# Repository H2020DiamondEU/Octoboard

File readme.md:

# Maximum Power Point Tracker for Research-Level Solar Cells

## Overview
This repository documents the design, implementation, and operation of a massively parallel, low-cost Maximum Power Point Tracker (MPPT) for aging and degradation studies of perovskite solar cells. The system integrates custom-designed PCBs and software for efficient tracking and data logging.

## Features
- **Hardware**:

  Octoboards (`Custom-designed PCBs`) for Source Measure Unit (SMU) functions
  - 8 channels per board
  - Modular and scalable design
  - Support for multiple boards via I2C addressing

  Measurement Chuck
   - Allows up to 10 substrates (40 solar cells on a "University of Marburg" cell layout) to be aged in a nitrogen atmosphere.
   - Compact design optimized to fit several chucks under standard solar simulators.  
   - Easy Sample Replacement: Single chucks within the setup can be exchanged during ongoing measurements without breaking the nitrogen atmosphere or interrupting the other measurements within the same sun simulator.  

- **Software**:

  Python-based control system
    - Efficient MPP tracking algorithm
    - Real-time data logging to CSV
    - Multi-board management
    
- **Integration**:

  Full Raspberry Pi compatibility for control and data acquisition

## Repository Structure
```plaintext
├── docs/
│   ├── images/
│   │   ├── EU_logo.png
│   │   ├── EU_logo_funding.png
│   │   ├── diamond_header.png
│   │   ├── octoboard.png
│   │   └── system.png
│   └── D5.2_100_ch_MPP_tracker.pdf
├── hardware/
│   ├── Measurement Chuck Housing CAD Design/
│   │   ├── Assembly.iam 
│   │   ├── Assembly.ipj 
│   │   ├── Bauteil4.ipt 
│   │   ├── Bauteil5.ipt
│   │   ├── Bauteil6.ipt
│   │   ├── chuck_v1.ipt
│   │   ├── DIN_EN_ISO_2338-3_h8x16.ipt 
│   │   ├── DIN_EN_ISO_4762-M2x3.ipt 
│   │   ├── DIN_EN_ISO_4762-M3x5.ipt 
│   │   ├── DIN_EN_ISO_4762-M3x10.ipt 
│   │   ├── DIN_EN_ISO_4762-M3x20.ipt 
│   │   ├── DIN_EN_ISO_7046-2_Z-M2.5x10-8.8-Z1.ipt 
│   │   ├── Glasscheibe.ipt 
│   │   ├── Glassubstrat_25x25x2.2.ipt 
│   │   └── Maske.ipt
│   ├── Measurement Chuck PCB Design/
│   │   ├── SubSheet.kicad_sch
│   │   ├── BOM.csv
│   │   ├── chuck_v1.dsn
│   │   ├── chuck_v1.kicad_pcb
│   │   ├── chuck_v1.kicad_prl
│   │   ├── chuck_v1.kicad_pro
│   │   ├── chuck_v1.kicad_sch
│   │   ├── CPL.csv
│   │   └── gerber.zip
│   ├── Octoboard PCB Design/
│   │   ├── DAC.kicad_sch
│   │   ├── octoboard.kicad_pcb
│   │   ├── octoboard.kicad_prl
│   │   ├── octoboard.kicad_pro
│   │   └── octoboard.kicad_sch
├── software/
│   ├── hardware/
│   │   ├── __init__.py
│   │   ├── channel.py
│   │   ├── constants.py
│   │   ├── i2c.py
│   │   ├── manager.py
│   │   ├── oboard.py
│   │   └── sdac.py
│   ├── tests/
│   │   ├── test_hardware.py
│   │   ├── test_logger.py
│   │   └── test_tracker.py
│   ├── __init__.py
│   ├── cli.py
│   ├── logger.py
│   ├── requirements.txt
│   └── setup.py
└── README.md
```

## Documentation

### 1. Hardware

#### **1.1 Octoboard**
The Octoboard is a custom-designed PCB that forms the core of the MPPT system, providing capabilities for maximum power point tracking in solar cell testing and evaluation.

**Key Components:**
- **MCP23017**: 16-bit I2C I/O expander for digital control
- **MCP4728**: 4-channel DAC for voltage control
- **ADS1115**: 16-bit ADC for precision measurement
- **LMV324**: Quad operational amplifiers for signal conditioning
- **74HC4051**: Analog multiplexers for efficient channel selection

#### Component Specifications

| Component | Type | Key Specifications | Datasheet |
|-----------|------|-------------------|-----------|
| MCP4728 | DAC | 12-bit, 4-channel, I2C | [Datasheet](http://ww1.microchip.com/downloads/en/devicedoc/22187e.pdf) |
| ADS1115 | ADC | 16-bit, 4-channel, I2C | [Datasheet](https://www.ti.com/lit/gpn/ads1115) |
| LMV324 | Op-Amp | Rail-to-rail, low power | [Datasheet](https://www.onsemi.com/download/data-sheet/pdf/lmv321-d.pdf) |
| 74HC4051 | Multiplexer | 8-channel analog | [Datasheet](https://assets.nexperia.com/documents/data-sheet/74HC_HCT4051.pdf) |
| MCP23017 | I/O Expander | 16-bit, I2C | [Datasheet](https://ww1.microchip.com/downloads/aemDocuments/documents/APID/ProductDocuments/DataSheets/MCP23017-Data-Sheet-DS20001952.pdf) |

#### System Architecture
The MPPT system is designed with a hierarchical structure:
1. Central Raspberry Pi controller
2. Multiple Octoboards (8 channels each)
3. I2C communication backbone
4. Integrated sample holder with thermal management

#### **1.2 Measurement Chuck**
The Measurement Chuck allows up to 10 substrates (40 solar cells on a "University of Marburg" cell layout) to be aged under a nitrogen atmosphere.
Due to its compact design, up to eight measurement chucks can be fit in a Solaronix SOLIXON A-45 solar simulator. 

**Operation & Handling**
To replace the substrates inside a chuck:
1. Disconnect the flat ribbon cables and nitrogen supply hoses (quick-connect couplings ensure that the remaining substrates stay in an N₂ atmosphere).
2. Transfer the chuck to a glovebox, where the cells can be exchanged by loosening the screws as shown in the video below.
3. Reinsert the newly equipped chuck into the sun simulator and attach it to the cables and supply hoses. 

<div style="display: flex; justify-content: flex-start;">
    
</div>

### 2. Software

#### Installation

1. Clone the repository:
```bash
git clone https://github.com/H2020DiamondEU/octoboard.git
cd octoboard
```

2. Install dependencies:
```bash
pip install -r software/requirements.txt
```

3. Install the package:
```bash
pip install -e .
```

#### Usage

1. Basic operation:
```python
from software import OBoardManager

# Initialize manager with I2C bus number
manager = OBoardManager(i2c_num=1)

# Start MPP tracking on all channels
manager.cycle_all_channels(iterations_per_channel=10)
```

2. Command-line interface:
```bash
python -m software.cli 1  # Start tracking on I2C bus 1
```

### 3. Data Management

Data is stored in CSV format with the following structure:
- Location: `data/[board_id]_channel_[n]_data.csv`
- Format: timestamp, voltage, current, power, temperature

### 4. Troubleshooting

Common issues and solutions:
1. I2C Communication Errors
   - Check bus number and device addresses
   - Verify cable connections
   - Check for address conflicts

2. Measurement Instability
   - Verify power supply stability
   - Check contact resistance

## License
This project is licensed under the MIT License. See `LICENSE` for details.

## Links
- [Project Website](https://diamond-horizon.eu/)
- [European Commission Project Page](https://cordis.europa.eu/project/id/101084124)
- [Deliverable Documentation](https://ec.europa.eu/research/participants/documents/downloadPublic?documentIds=080166e50d1470c5&appId=PPGMS)

## Contact
For further information on integrating this measurement system into your PV lab, please contact:
- **Lukas Wagner**, Physics of Solar Energy Conversion Group, Philipps-University Marburg, Germany.
- **Clemens Baretzky**, Fraunhofer Institute for Solar Energy Systems ISE, Germany.

<div style="display: flex; justify-content: flex-start;">
    
</div> 

## Acknowledgments
This design was developed at the **University of Marburg** and **Fraunhofer ISE**.
The project is funded by the European Union in the Horizon 2.5. Climate, Energy and Mobility programme under Grant Agreement No. 101084124. Views and opinions expressed are however those of the author(s) only and do not necessarily reflect those of the European Union. Neither the European Union nor the granting authority can be held responsible for them.

<div style="display: flex; justify-content: flex-start;">
    
</div>

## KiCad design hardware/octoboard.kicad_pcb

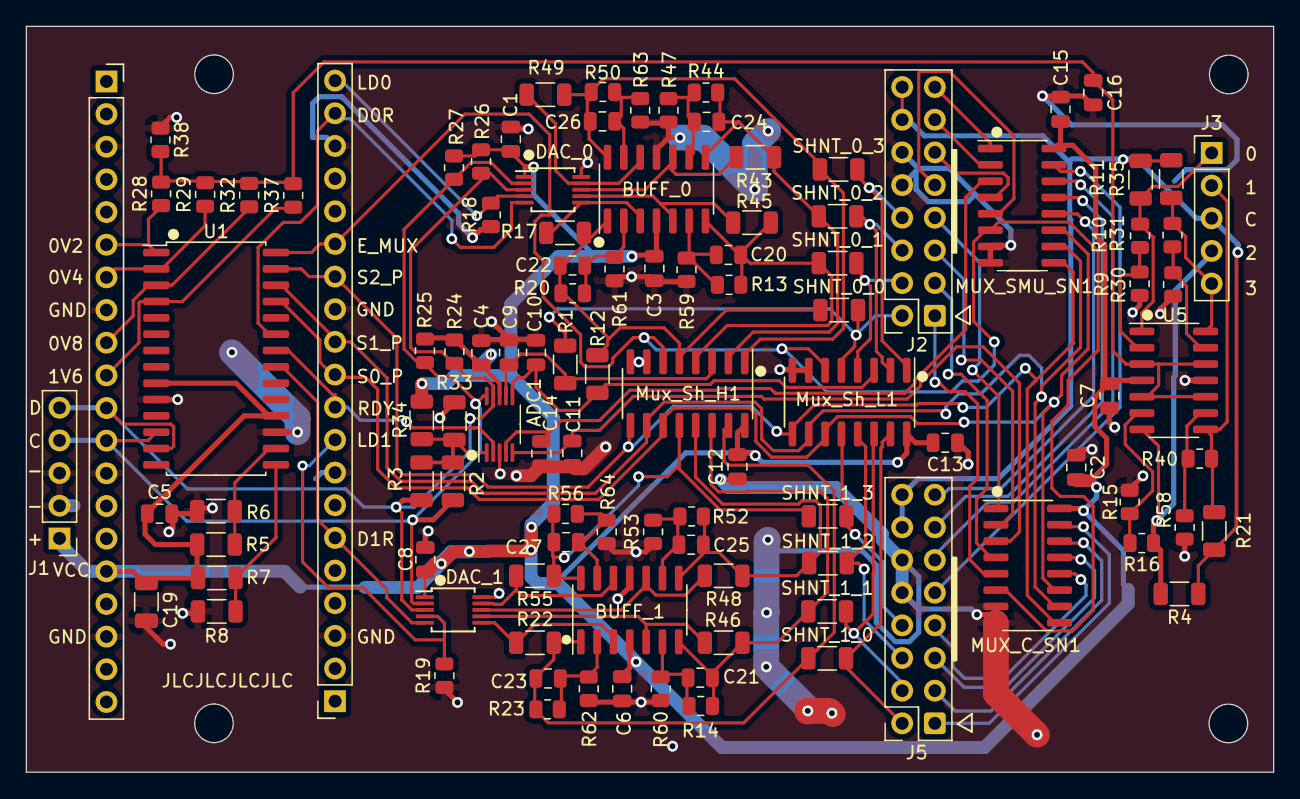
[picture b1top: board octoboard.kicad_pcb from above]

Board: 2 copper layers, 97.0 x 58.0 mm, 107 parts (0 on the bottom side), 82 nets.

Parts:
ADC1: ADS1115IDGS; VSSOP-10_3x3mm_P0.5mm
BUFF_0, BUFF_1: LMV324; SOIC-14_3.9x8.7mm_P1.27mm
C1, C2, C3, C4, C5, C6, C7, C8, C9, C10, C11, C12, C13, C14, C15, C16: 0.1µ; C_0805_2012Metric
C19: 1µ; C_1206_3216Metric
C20, C21, C22, C23, C24, C25, C26, C27: 22p; C_0805_2012Metric
DAC_0, DAC_1: MCP4728; MSOP-10_3x3mm_P0.5mm
J1, J3: Conn_01x05_Pin; PinHeader_1x05_P2.54mm_Vertical
J2, J5: Conn_02x08_Odd_Even; IDC-Header_2x08_P2.54mm_Vertical_NO_SHROUD
MUX_C_SN1: 74HC4051; SOIC-16_3.9x9.9mm_P1.27mm
MUX_SMU_SN1: 74HC4051; SOIC-16_3.9x9.9mm_P1.27mm
Mux_Sh_H1: 74HC4051; SOIC-16_3.9x9.9mm_P1.27mm
Mux_Sh_L1: 74HC4051; SOIC-16_3.9x9.9mm_P1.27mm
R1, R2, R3, R5, R6, R7, R8, R12, R17, R22, R33, R34, R43, R45, R46, R48, R49, R55: 0; R_1206_3216Metric
R4, R11, R21, R35: 10; R_1206_3216Metric
R9, R10, R13, R14, R15, R16, R20, R23, R30, R31, R40, R44, R47, R50, R52, R53, R56, R58, R59, R60, R61, R62, R63, R64: 12k; R_0805_2012Metric
R18, R19, R28: 47k; R_0805_2012Metric
R24, R25, R26, R27, R37: 4.7K; R_0805_2012Metric
R29: 22k; R_0805_2012Metric
R32, R38: 10k; R_0805_2012Metric
RPI_20, RPI_40: Conn_01x20_Female; PinSocket_1x20_P2.54mm_Vertical
SHNT_0_0, SHNT_0_1, SHNT_0_2, SHNT_0_3, SHNT_1_0, SHNT_1_1, SHNT_1_2, SHNT_1_3: 20; R_1206_3216Metric
U1: MCP23017_SO; SOIC-28W_7.5x17.9mm_P1.27mm
U5: LMV324DR2G; SOIC-14_3.9x8.7mm_P1.27mm

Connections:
+3.3V: ADC1.8 (VDD), BUFF_0.4 (V+), BUFF_1.4 (V+), C1.2, C2.2, C3.2, C4.1, C5.1, C6.2, C7.2, C8.2, C12.2, C13.2, C15.2, C19.2, DAC_0.1 (VDD), DAC_1.1 (VDD), J1.1, MUX_C_SN1.16 (VCC), MUX_SMU_SN1.16 (VCC), Mux_Sh_H1.16 (VCC), Mux_Sh_L1.16 (VCC), R5.2, R7.2, R24.2, R25.2, R26.2, R27.2, R34.2, RPI_20.16, U1.9 (VDD), U1.18 (~RESET), U5.4 (V+)
A0_mult: ADC1.4 (AIN0), C14.2, MUX_SMU_SN1.3 (A)
A1_mult: ADC1.5 (AIN1), C11.2, MUX_C_SN1.3 (A)
A2_mult: ADC1.6 (AIN2), C10.2, Mux_Sh_L1.3 (A), R12.1
A3_mult: ADC1.7 (AIN3), C9.2, Mux_Sh_H1.3 (A), R1.1
ADC_1_RDY: ADC1.2 (ALERT/RDY), RPI_40.10, U1.22 (GPA1)
C_SENS_0_0: J2.1, MUX_C_SN1.5 (A5)
C_SENS_0_1: J2.3, MUX_C_SN1.4 (A7)
C_SENS_0_2: J2.5, MUX_C_SN1.2 (A6)
C_SENS_0_3: J2.7, MUX_C_SN1.1 (A4)
C_SENS_1_0: J5.1, MUX_C_SN1.15 (A2)
C_SENS_1_1: J5.3, MUX_C_SN1.14 (A1)
C_SENS_1_2: J5.5, MUX_C_SN1.13 (A0)
C_SENS_1_3: J5.7, MUX_C_SN1.12 (A3)
DAC_0_LDAC: DAC_0.4 (~LDAC), R18.2, RPI_40.20
DAC_0_RDY: DAC_0.5 (RDY/~BSY), RPI_40.19, U1.23 (GPA2)
DAC_1_LDAC: DAC_1.4 (~LDAC), R19.2, RPI_40.9
DAC_1_RDY: DAC_1.5 (RDY/~BSY), RPI_40.6, U1.21 (GPA0)
DAC_BUFF_0_0: BUFF_0.1, C22.2, Mux_Sh_H1.5 (A5), R12.2, R17.2, R20.2, SHNT_0_0.1
DAC_BUFF_0_1: BUFF_0.7, C20.2, Mux_Sh_H1.4 (A7), R13.2, R45.2, SHNT_0_1.1
DAC_BUFF_0_2: BUFF_0.8, C24.2, Mux_Sh_H1.2 (A6), R43.2, R44.2, SHNT_0_2.1
DAC_BUFF_0_3: BUFF_0.14, C26.2, Mux_Sh_H1.1 (A4), R49.2, R50.2, SHNT_0_3.1
DAC_BUFF_1_0: BUFF_1.1, C23.2, Mux_Sh_H1.15 (A2), R22.2, R23.2, SHNT_1_0.1
DAC_BUFF_1_1: BUFF_1.7, C21.2, Mux_Sh_H1.14 (A1), R14.2, R46.2, SHNT_1_1.1
DAC_BUFF_1_2: BUFF_1.8, C25.2, Mux_Sh_H1.13 (A0), R48.2, R52.2, SHNT_1_2.1
DAC_BUFF_1_3: BUFF_1.14, C27.2, Mux_Sh_H1.12 (A3), R55.2, R56.2, SHNT_1_3.1
E_mult_1: MUX_C_SN1.6 (~E), MUX_SMU_SN1.6 (~E), Mux_Sh_H1.6 (~E), Mux_Sh_L1.6 (~E), RPI_40.15, U1.28 (GPA7)
GND: ADC1.3 (GND), BUFF_0.11 (V-), BUFF_1.11 (V-), C1.1, C2.1, C3.1, C4.2, C5.2, C6.1, C7.1, C8.1, C9.1, C10.1, C11.1, C12.1, C13.1, C14.1, C15.1, C16.2, C19.1, DAC_0.10 (VSS), DAC_1.10 (VSS), J1.2, J1.3, J2.10, J2.12, J5.10, J5.12, MUX_C_SN1.7 (VEE), MUX_C_SN1.8 (GND), MUX_SMU_SN1.7 (VEE), MUX_SMU_SN1.8 (GND), Mux_Sh_H1.7 (VEE), Mux_Sh_H1.8 (GND), Mux_Sh_L1.7 (VEE), Mux_Sh_L1.8 (GND), R6.1, R8.1, R9.1, R15.1, R18.1, R19.1, R30.1, R33.2, R38.1, R47.1, R53.1, R58.1, R59.1, R60.1, R61.1, R62.1, R63.1, R64.1, RPI_20.3, RPI_20.8, RPI_20.13, RPI_20.18, RPI_40.3, RPI_40.8, RPI_40.13, RPI_40.18, U1.10 (VSS), U1.17 (A2), U5.11 (V-)
I2C0_SCL: ADC1.10 (SCL), DAC_0.2 (SCL), DAC_1.2 (SCL), J1.4, R2.2, R25.1, R27.1, RPI_20.12, U1.12 (SCK)
I2C0_SDA: ADC1.9 (SDA), DAC_0.3 (SDA), DAC_1.3 (SDA), J1.5, R3.2, R24.1, R26.1, RPI_20.11, U1.13 (SDA)
unnamed: ADC1.1 (ADDR), R2.1, R3.1, R33.1, R34.1
unnamed: BUFF_0.3 (+), DAC_0.6 (VOUTA), R17.1
unnamed: BUFF_0.2 (-), C22.1, R20.1, R61.2
unnamed: BUFF_0.5 (+), DAC_0.7 (VOUTB), R45.1
unnamed: BUFF_0.6 (-), C20.1, R13.1, R59.2
unnamed: BUFF_0.10 (+), DAC_0.8 (VOUTC), R43.1
unnamed: BUFF_0.9 (-), C24.1, R44.1, R47.2
unnamed: BUFF_0.12 (+), DAC_0.9 (VOUTD), R49.1
unnamed: BUFF_0.13 (-), C26.1, R50.1, R63.2
unnamed: BUFF_1.3 (+), DAC_1.6 (VOUTA), R22.1
unnamed: BUFF_1.2 (-), C23.1, R23.1, R62.2
unnamed: BUFF_1.5 (+), DAC_1.7 (VOUTB), R46.1
unnamed: BUFF_1.6 (-), C21.1, R14.1, R60.2
unnamed: BUFF_1.10 (+), DAC_1.8 (VOUTC), R48.1
unnamed: BUFF_1.9 (-), C25.1, R52.1, R53.2
unnamed: BUFF_1.12 (+), DAC_1.9 (VOUTD), R55.1
unnamed: BUFF_1.13 (-), C27.1, R56.1, R64.2
unnamed: R7.1, R8.2, U1.15 (A0)
unnamed: R5.1, R6.2, U1.16 (A1)
unnamed: C16.1, R28.2, R29.2, R32.2, R37.2, R38.2, U5.3 (+), U5.5 (+), U5.10 (+), U5.12 (+)
unnamed: R9.2, R10.1, U5.2 (-)
unnamed: R15.2, R16.1, U5.6 (-)
unnamed: R40.1, R58.2, U5.9 (-)
unnamed: R30.2, R31.1, U5.13 (-)
S0_PLX: MUX_C_SN1.11 (S0), MUX_SMU_SN1.11 (S0), Mux_Sh_H1.11 (S0), Mux_Sh_L1.11 (S0), RPI_40.11, U1.25 (GPA4)
S1_PLX: MUX_C_SN1.10 (S1), MUX_SMU_SN1.10 (S1), Mux_Sh_H1.10 (S1), Mux_Sh_L1.10 (S1), RPI_40.12, U1.26 (GPA5)
S2_PLX: MUX_C_SN1.9 (S2), MUX_SMU_SN1.9 (S2), Mux_Sh_H1.9 (S2), Mux_Sh_L1.9 (S2), RPI_40.14, U1.27 (GPA6)
SDAC_A_0V2: R28.1, RPI_20.6, U1.1 (GPB0)
SDAC_A_0V4: R29.1, RPI_20.7, U1.2 (GPB1)
SDAC_B_0V8: R32.1, RPI_20.9, U1.3 (GPB2)
SDAC_B_1V6: R37.1, RPI_20.10, U1.4 (GPB3)
SDAC_V0: J3.1, R10.2, R11.2, U5.1
SDAC_V1: J3.2, R21.2, R40.2, U5.8
SDAC_V2: J3.4, R4.2, R16.2, U5.7
SDAC_V3: J3.5, R31.2, R35.2, U5.14
SMU_Common: J2.14, J2.16, J3.3, J5.14, J5.16, R4.1, R11.1, R21.1, R35.1
SMU_OUT_0_0: J2.2, Mux_Sh_L1.5 (A5), R1.2, SHNT_0_0.2
SMU_OUT_0_1: J2.4, Mux_Sh_L1.4 (A7), SHNT_0_1.2
SMU_OUT_0_2: J2.6, Mux_Sh_L1.2 (A6), SHNT_0_2.2
SMU_OUT_0_3: J2.8, Mux_Sh_L1.1 (A4), SHNT_0_3.2
SMU_OUT_1_0: J5.2, Mux_Sh_L1.15 (A2), SHNT_1_0.2
SMU_OUT_1_1: J5.4, Mux_Sh_L1.14 (A1), SHNT_1_1.2
SMU_OUT_1_2: J5.6, Mux_Sh_L1.13 (A0), SHNT_1_2.2
SMU_OUT_1_3: J5.8, Mux_Sh_L1.12 (A3), SHNT_1_3.2
SMU_SENS_0_0: J2.9, MUX_SMU_SN1.5 (A5)
SMU_SENS_0_1: J2.11, MUX_SMU_SN1.4 (A7)
SMU_SENS_0_2: J2.13, MUX_SMU_SN1.2 (A6)
SMU_SENS_0_3: J2.15, MUX_SMU_SN1.1 (A4)
SMU_SENS_1_0: J5.9, MUX_SMU_SN1.15 (A2)
SMU_SENS_1_1: J5.11, MUX_SMU_SN1.14 (A1)
SMU_SENS_1_2: J5.13, MUX_SMU_SN1.13 (A0)
SMU_SENS_1_3: J5.15, MUX_SMU_SN1.12 (A3)

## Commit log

2025-02-10 Added some files and updated readme.md
2025-02-10 changed logo
2025-02-10 improved image quality of Logo
2025-02-10 Corrected some typos
2025-02-11 Changed logos
2025-03-07 added doi tag to readme.md
2025-03-07 fixed doi placement readme.md
2025-03-19 Add files via upload
    Changed logos
2025-03-19 Update readme.md
    Updated to show logos of Fraunhofer and ISE side by side
2025-05-18 Create examples.md
    Added a subfolder to present examples of implementation
2025-05-18 Create readme.md
    Added a readme for the GUI used with the Marburg measureing setup
2025-05-18 Add files via upload
    Added a preliminary upload of the Marburg GUI
